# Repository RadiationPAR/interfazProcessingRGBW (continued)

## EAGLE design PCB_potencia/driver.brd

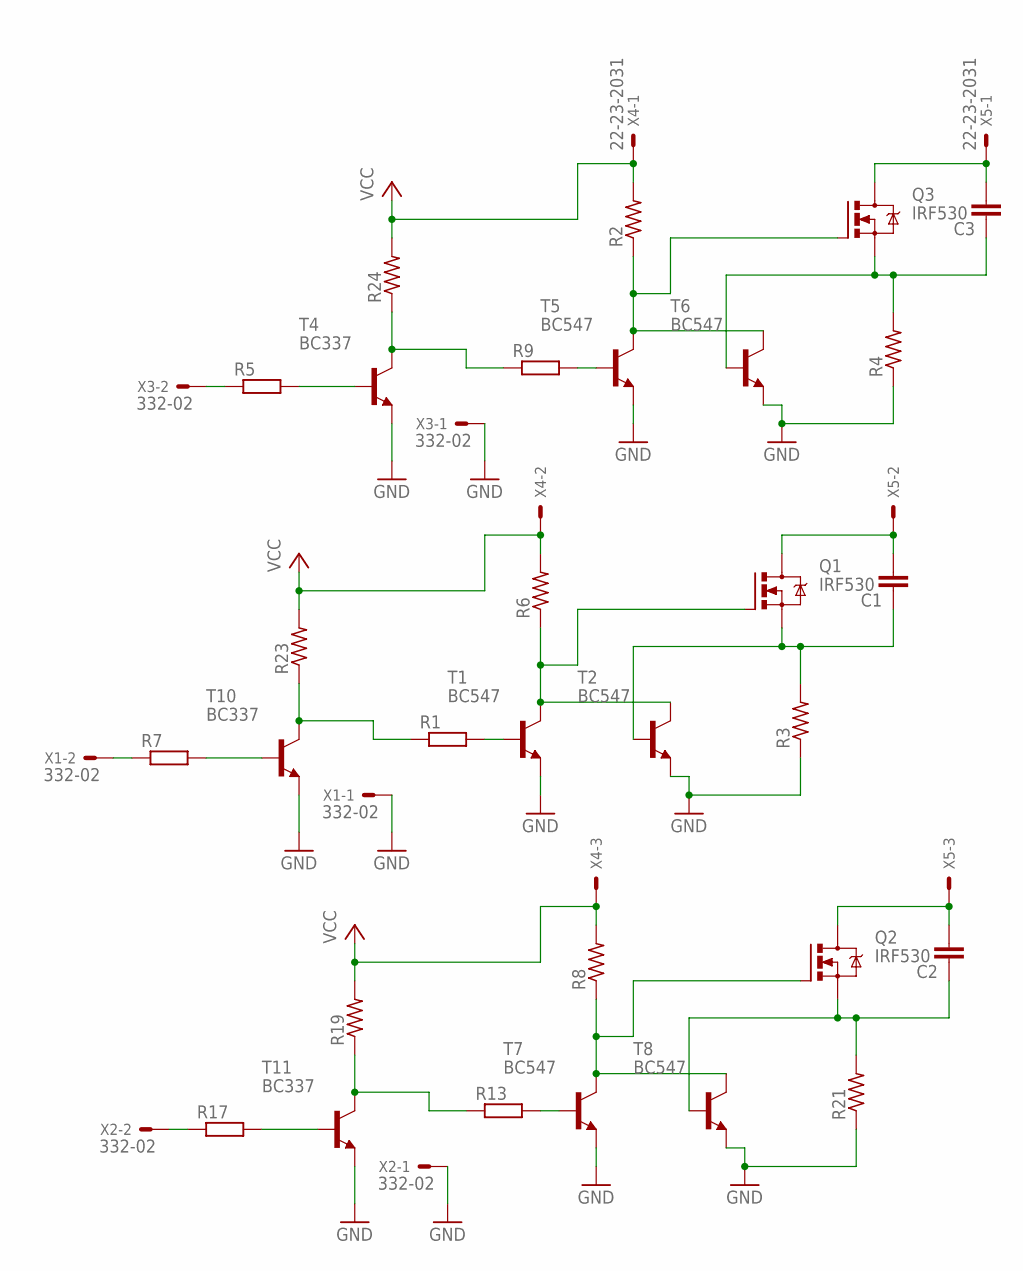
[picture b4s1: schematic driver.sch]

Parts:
C1, C2, C3: C-EU025-025X050; C025-025X050
Q1, Q2, Q3: IRF530; TO220BV
R1, R9, R13: R0204/7; 0204/7
R2, R6, R8, R19, R23, R24: R-US_0309/10; 0309/10
R3, R4, R21: R-US_0817/22; P0817/22
R5, R7, R17: R-EU_0204/7; 0204/7
T1, T2, T5, T6, T7, T8: BC547; TO92
T4, T10, T11: BC337; TO92
X1, X2, X3: 332-02
X4, X5: 22-23-2031

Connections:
GND: R3.1, R4.1, R21.1, T1.1 (E), T2.1 (E), T4.1 (E), T5.1 (E), T6.1 (E), T7.1 (E), T8.1 (E), T10.1 (E), T11.1 (E), X1.1, X2.1, X3.1
unnamed: R1.2, T1.2 (B)
unnamed: Q1.G, R6.1, T1.3 (C), T2.3 (C)
unnamed: C1.2, Q1.D, X5.2
unnamed: R5.2, T4.2 (B)
unnamed: C1.1, Q1.S, R3.2, T2.2 (B)
unnamed: R7.2, T10.2 (B)
unnamed: R9.1, R24.1, T4.3 (C)
unnamed: R5.1, X3.2
unnamed: R1.1, R23.1, T10.3 (C)
unnamed: R7.1, X1.2
unnamed: R13.2, T7.2 (B)
unnamed: R9.2, T5.2 (B)
unnamed: Q3.G, R2.1, T5.3 (C), T6.3 (C)
unnamed: C3.2, Q3.D, X5.1
unnamed: C3.1, Q3.S, R4.2, T6.2 (B)
unnamed: Q2.G, R8.1, T7.3 (C), T8.3 (C)
unnamed: C2.2, Q2.D, X5.3
unnamed: C2.1, Q2.S, R21.2, T8.2 (B)
unnamed: R17.2, T11.2 (B)
unnamed: R13.1, R19.1, T11.3 (C)
unnamed: R17.1, X2.2
VCC: R2.2, R6.2, R8.2, R19.2, R23.2, R24.2, X4.1, X4.2, X4.3

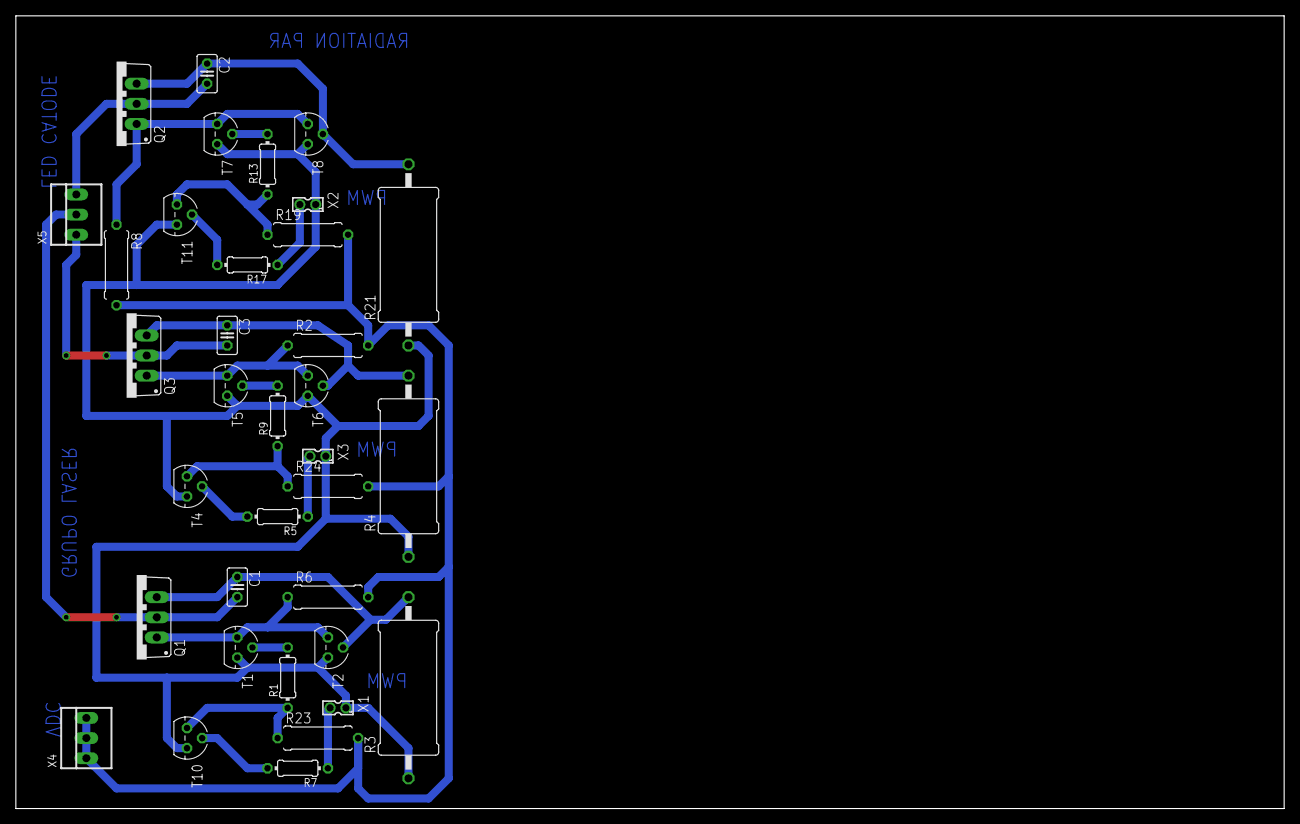
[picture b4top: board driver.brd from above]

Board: 2 copper layers, 160.0 x 100.0 mm, 35 parts (0 on the bottom side), 23 nets.

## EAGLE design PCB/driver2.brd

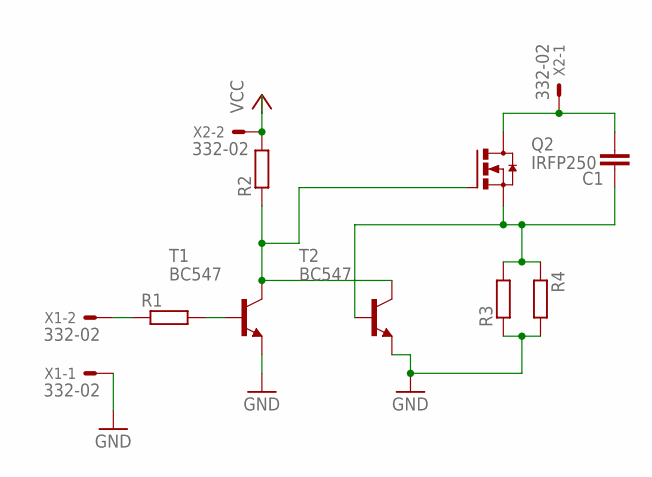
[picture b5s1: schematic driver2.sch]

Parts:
C1: C-EU025-025X050; C025-025X050
Q2: IRFP250; TO-247AD-V
R1, R2, R3, R4: R0204/7; 0204/7
T1, T2: BC547; TO92
X1, X2: 332-02

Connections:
GND: R3.1, R4.2, T1.1 (E), T2.1 (E), X1.1
unnamed: R1.1, X1.2
unnamed: R1.2, T1.2 (B)
unnamed: Q2.G, R2.1, T1.3 (C), T2.3 (C)
unnamed: C1.2, Q2.D, X2.1
unnamed: C1.1, Q2.S, R3.2, R4.1, T2.2 (B)
VCC: R2.2, X2.2

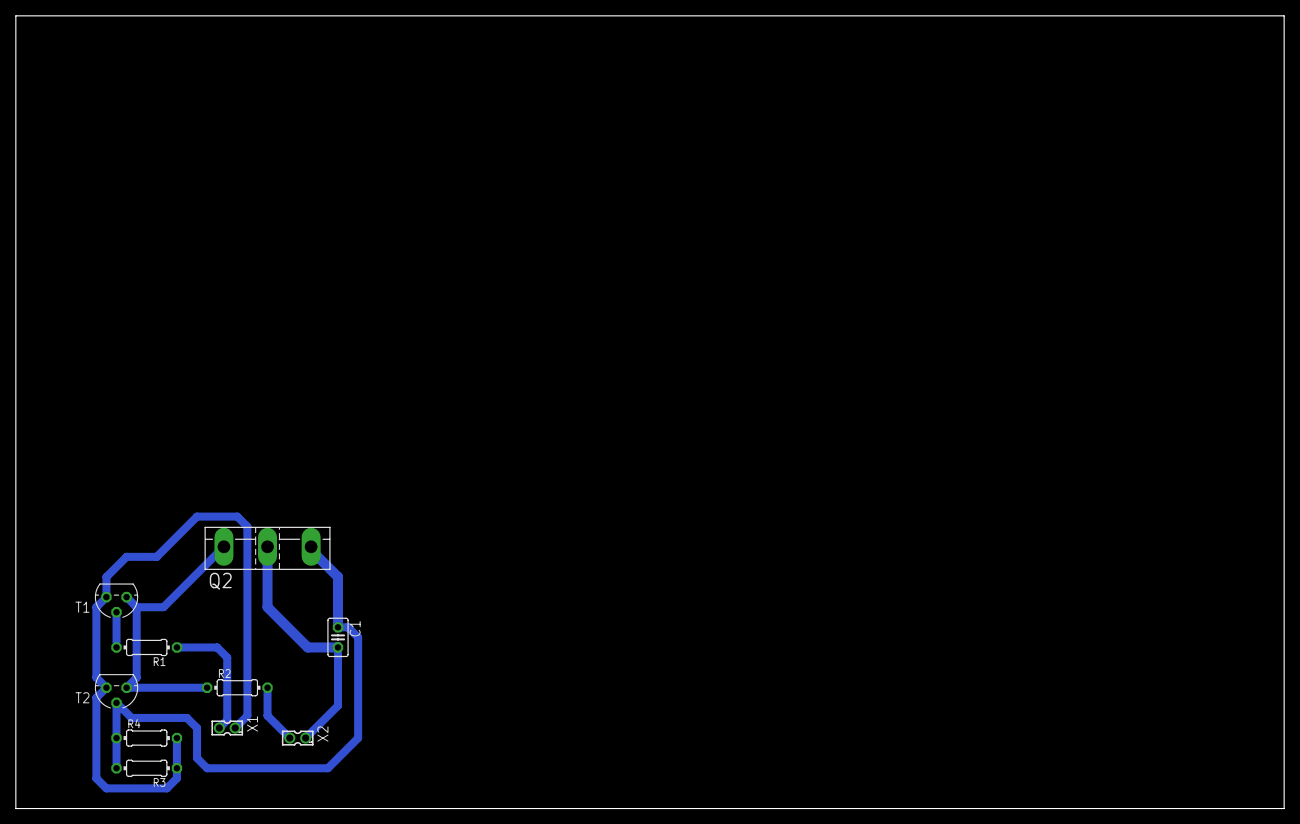
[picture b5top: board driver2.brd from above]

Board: 2 copper layers, 160.0 x 100.0 mm, 10 parts (0 on the bottom side), 7 nets.

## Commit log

2016-05-07 Se añade el fichero multimedia de imagenes, recurso para interfaz processing
2016-05-07 Se añade codigo fuente y librerias para interfaz RGBW ejecutable por processing
2016-05-07 Se añade codigo fuente para micro Tiva, generador de 4 PWM y comunicación por puerto serial a processing
2016-05-07 Se añade codigo fuente para lectura del sensor de color TCS3220 empleando el micro Tiva
2016-05-07 Se recuperan comentarios del primer repositorio
2016-05-07 Actualización del README
2016-05-31 Se añade paleta de colores usando D3 para pruebas del TCS3220
2016-07-03 Se unen los fragmentos de codigo del sensor y el control RGBW
2016-07-11 Se añade diseño PCB de potencia para un arreglo (canal) matricial de leds
2016-07-13 Se añaden funciones de teclado y lectura de puerto serial RS-232
2016-07-16 Se añade diseño PCB driver de potencia RGB
2016-07-17 Se modifica por software la potencia del canal R
2016-07-27 Se corrige transistor para invertir la señal de cada PWM y se ajustan resistencias de potencia
2016-07-31 Se mejora funcion de lectura de caracteres ascii enviados por puerto serial desde la interfaz al micro y se añade funcion de escritura por puerto serial
2016-07-31 Se ordena y se añaden comentarios al codigo fuente de la interfaz en Processing
2016-08-01 Se modifica nombre del fichero por inconsistencias a la hora de lanzar la interfaz
2016-08-01 Se añaden ficheros de pruebas de calibracion con Módulo de Iluminación en Laboratorio de Ensayos Eléctricos Industriales de la Universidad Nacional
2016-08-01 Se añade función tipo struct para la creación de un objeto
2016-08-01 Se modifica la clase SliderV, se normalizan datos enviados a porcentaje, se modifica fichero de imagenes
2016-08-02 Indentaciones y función promediador de variables en struct
2016-08-02 se corrige promediador y se imprime caracteres en estándar rfc2616
2016-08-02 Se ordena el código por funciones y fix imagen croma
2016-08-02 se añade lector del get con diccionario(MAP)
2016-08-02 Se pone color capturado como fondo de Grilla
2016-08-04 Se añade funcion para evento Serial, se corrige escritura de datos PWM
2016-08-04 Se leen los 4 Canales N veces antes de RGB/timeout a pulseIn
2016-08-04 Se añade recta angular para representar un dato RGB en Matiz (angulo) útil para la interfaz del croma
2016-08-04 Se cambia imagen del espectro visible, se añaden funciones para obtener la matiz de un color RGB y representarla con un trazo angular sobre la imagen croma
2016-08-07 Se añaden calculos para obtener iluminancia y saturacion del color
2016-08-07 Se modifica nombre del fichero HSV-HSL Hue Saturation Luminance
2016-08-08 Se añaden lineas de codigo para obtener la posicion de un color RGB a XYZ
2016-08-08 Se añaden lineas de codigo para obtener la representacion CMY (Cian, Magent,Yellow) de un color RGB
2016-08-12 Se añaden diagramas de bloques para la comprension de codigos fuente del microcontrolador como de la interfaz
2016-08-16 Se añade funcion para conversiones de RGB-HSL, RGB-CMY, RGB-XYZ y se pinta un trazo angular para representar la matiz sobre la imagen croma
2016-08-16 Se añaden labels de texto para mostrar en interfaz las conversiones de RGB
2016-08-16 Se pinta onda senoidal del color capturado por el sensor, se rota 90 grados la imagen croma para usar como referencia el 0 grados geometrico y se añade una fotografia del PCB
2016-08-16 Se expresan en porcentajes algunos valores necesarios como C,M,Y,saturacion,luminancia y se deja en grados la matiz
2016-09-14 Se cargan archivos de diseño PCB con el empaquetado del microcontrolador
2016-09-14 Se elimina ficheros PCB y visorWEB
2016-09-21 Se añade PCB final
2016-12-02 Instrucciones raspberry en el readme
2016-12-08 Se deja por definicion la licencia GPL 3.0 para llevar el proyecto al open hardware design
2016-12-09 se añade funcion para el manejo de fecha y hora
2016-12-13 Queda lista la visualizacion de fecha y hora sobre la interfaz obteniendo el año,mes,dia,hora,min,seg desde el timmer de la raspberry
2017-01-26 Set theme jekyll-theme-hacker
2017-01-26 Set theme jekyll-theme-leap-day
2017-04-06 Se añade lista de componentes para circuito de control
2017-08-20 Se ajusta el codigo para trabajar el microcontrolador Tiva C Series TM4C123G usando Atom/platformio y se eliminan archivos de poco interes
2017-09-24 Einstein
2017-10-02 Cambio Estilos
2017-10-13 Se añade simulacion base del circuito de potencia, se actualizan codigos de interfaz y microcontrolador
2017-10-13 se cargan pruebas de medicion realizadas en el laboratorio de la Universidad Nacional
2018-08-25 se carga diseño pcb alternativo
